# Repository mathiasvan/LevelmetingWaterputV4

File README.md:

# Levelmeting Waterput V4

## Description

This project is V4 in the levelmeting waterput project. It uses the [QDY30A level sensor with RS485 protocol](https://nl.aliexpress.com/item/1005004940352922.html?srcSns=sns_Copy&spreadType=socialShare&bizType=ProductDetail&social_params=60985872337&aff_fcid=d36cea4a44db45c6bede2523cc9afb1e-1753980282806-07628-_EjQJvbW&tt=MG&aff_fsk=_EjQJvbW&aff_platform=default&sk=_EjQJvbW&aff_trace_key=d36cea4a44db45c6bede2523cc9afb1e-1753980282806-07628-_EjQJvbW&shareId=60985872337&businessType=ProductDetail&platform=AE&terminal_id=5ec7fe4f4f894db8bbb9257240edc8ba&afSmartRedirect=y) because all the previous sensors broke.

This project uses the [ModbusMaster library](https://github.com/4-20ma/ModbusMaster/tree/master) which can be installed from the Library Manager in the Arduino IDE.

## Components

- Sensor is the [QDY30A level sensor with RS485 protocol](https://nl.aliexpress.com/item/1005004940352922.html?srcSns=sns_Copy&spreadType=socialShare&bizType=ProductDetail&social_params=60985872337&aff_fcid=d36cea4a44db45c6bede2523cc9afb1e-1753980282806-07628-_EjQJvbW&tt=MG&aff_fsk=_EjQJvbW&aff_platform=default&sk=_EjQJvbW&aff_trace_key=d36cea4a44db45c6bede2523cc9afb1e-1753980282806-07628-_EjQJvbW&shareId=60985872337&businessType=ProductDetail&platform=AE&terminal_id=5ec7fe4f4f894db8bbb9257240edc8ba&afSmartRedirect=y).
- [MAX485 module](https://nl.aliexpress.com/item/1005009235324836.html?spm=a2g0o.productlist.main.18.6f7028e663hk5b&algo_pvid=be4b66e5-2800-47ac-b6a6-58f13e3ffc2b&algo_exp_id=be4b66e5-2800-47ac-b6a6-58f13e3ffc2b-17&pdp_ext_f=%7B%22order%22%3A%22-1%22%2C%22eval%22%3A%221%22%7D&pdp_npi=4%40dis%21EUR%2117.32%215.53%21%21%21139.11%2144.42%21%40211b430817539750750754094efdc0%2112000048420270373%21sea%21BE%210%21ABX&curPageLogUid=VVom2pkc4jR8&utparam-url=scene%3Asearch%7Cquery_from%3A) so that the Arduino/ESP32 can communicate with the modbus protocol by using the RX and TX pins.
- AZDelivery ESP32 Dev Kit C V4 for wireless data transmission which I had lying around.
- [220-240V to 24V power adapter](https://www.amazon.com.be/-/en/Universal-Adapter-220-240V-Inverter-Converter/dp/B0DRP7CS6Y/ref=sr_1_6?crid=1ACSXPUVS5M3O&dib=eyJ2IjoiMSJ9.FTbxj5E1wm82PugM4UbSTGT1U-mJWSjutiHkte5HbkOeKfQrB-BOpuIBgImuRtzR-Oxsbv6aAav57drT663OdneUMQ0v3lXwz_fyhLJ6fqaBDiDpmi3t64ZKGnJhwVYG2fniTcgwXYQBbRFDHbBWO10F0hNb3RetDSqDfkFQakxUy2J-pAYLw4MWh0_5NM9YgepXiq3lA2xNkwteyM8PkXWb3mjuG0ey11ltC3uAtEaBidy8vM2pcyvCirzr-JK_tczkhxNdXqsYSO3U6uUHg2HoZKGJPsb2ADYXPQJMeao.7CeGK0aJhAgOUL4NGwdO5NkmGQ1lxo9eezmmLnGFa6c&dib_tag=se&keywords=240v%2BAC%2Bto%2B24v%2Bdc%2Badapter&qid=1756312614&sprefix=240v%2Bac%2Bto%2B24v%2Bdc%2Badapter%2Caps%2C95&sr=8-6&th=1) as the sensor works on 24V.
- [24V to 5V step-down converter](https://www.amazon.com.be/-/en/Heemol-Converter-Module-DC-DC-Power/dp/B0BCV6GRH5/ref=sr_1_3?crid=1N3TF49LMAD7M&dib=eyJ2IjoiMSJ9.q-0kuL72pe2IKbCABHzv8yXOsoQ4-v-Wq0jyu740BLkh13zqbLLy1FTG98uMWzEd8oz7OTgdK4OSP_4BK1gTu9wjp9CoapG2o3FZpXtIWlHqLC9P6f17gwq7Obhck1AqX469Dt1Ga9VJU1P0AJyKzVB0Ln-N5Ue2JrF5tVuZJ5tERdzsEsNTRxSBOX8tx5-2qo5J622tHXK5aL6bRXPW_Zn6CSXFCy_SFn3BGmzdMCV8JSYf2uHlnAjMfwTZvKOJRcqpMr4RmKVLJPQKJ-YGLqcOWeauEC0VQ_aWCukiv7Q.-T0r3asJ5W8xXmG-Gu4cFkVHnN3vhC2m68qT4c__YZo&dib_tag=se&keywords=dc+dc+24+to+5v+converter&qid=1756310998&sprefix=dc+dc+24+to+5v+converter%2Caps%2C92&sr=8-3) to power the ESP32. The MAX485 module is powered by the 5V pin of the ESP32.

## Diagram

Thanks lejmr for this diagram. I used it to test my sensor. It is wrong for the TX and RX pins, they should be swapped. (See below for more.) The rest is the same as in this diagram.

My adaptation:
I used pin 2 on the ESP32 to connect the DE and RE pins from the MAX485 module.

See the final KiCad diagram under the `waterputv4Schematics` folder. Here is a screenshot in case you don't have KiCad.

## Testing the sensor

This took a lot of trial and error but I got it working in the end. Some important remarks:

1. R0 from the MAX485 module should be connected to RX on the ESP32 and DI to TX. This is wrong in the original diagram I used.
2. The provided screw terminals on the MAX485 module are useful to connect the sensor to.
3. You cannot use the Serial port for debugging as you need the TX and RX pins to communicate with the sensor. I used the Bluetooth Serial library instead. You need to download the Bluetooth Serial app on your phone to connect to the wireless Serial.
4. When uploading the code, disconnect TX, RX, 5V and GND from the MAX485 and ESP32.
5. The test code is in the folder `testcode`.

## Final integration

- I have been using ThingSpeak for all the previous versions and it works quite well to store the data.
- The Bluetooth Serial library took too much space, so I have switched to the TelnetStream library. You need to install PuTTY and enter the IP adress which can be obtained from the Serial monitor. After this, it connects to the modbus sensor and from that moment on, all logging will happen with the telnet stream on PuTTY.
- You need to add a `credentials.h` file in the same folder as the final code. You need to fill this template with your own credentials.

```c++
#define mySSID "xxxxx"
#define myPASSWORD "xxxxx"
#define myChannelNumber 111111
#define myWriteAPIKey "xxxxxx"
```

## Telnet Commands

After connecting to your ESP32 using PuTTY (see IP address in Serial Monitor), you can use the following commands in the telnet console:

- **ping**  
  The ESP32 will respond with `pong`, show the current sensor height, and display the time remaining until the next automatic data upload to ThingSpeak.

- **send data**  
  Immediately triggers a sensor reading and uploads the value to ThingSpeak, regardless of the regular upload interval.

**Example session:**

```
> ping
pong
Doing a height reading...
Data at adress 4: 158
Converted height: 15.8cm
15.80
Time to next data send: 122 seconds

> send data
Sending data now...
Data at adress 4: 158
Converted height: 15.8cm
Height: 15.8cm
Uploading data to ThingSpeak...
Successful upload to ThingSpeak.
Height: 15.80 uploaded to ThingSpeak server.

```

If you enter an unknown command, nothing will happen. Commands are case-sensitive.

**Tip:**  
Make sure you have connected to the correct IP address and that your ESP32 is powered and connected to WiFi.

## Wishlist

- [ ] Add `reconnect wifi` command.
- [ ] OTA updates

## Resources

- [Datasheets that came in the box](https://h5.hlcode.com.cn/?id=NK1LFtJ&f=wx)
- [Thanks a lot to lejmr for this project!](https://github.com/lejmr/dyi-ha-water-management)
- [This tutorial has helped me a lot](https://how2electronics.com/how-to-use-modbus-rtu-with-esp32-to-read-sensor-data/)

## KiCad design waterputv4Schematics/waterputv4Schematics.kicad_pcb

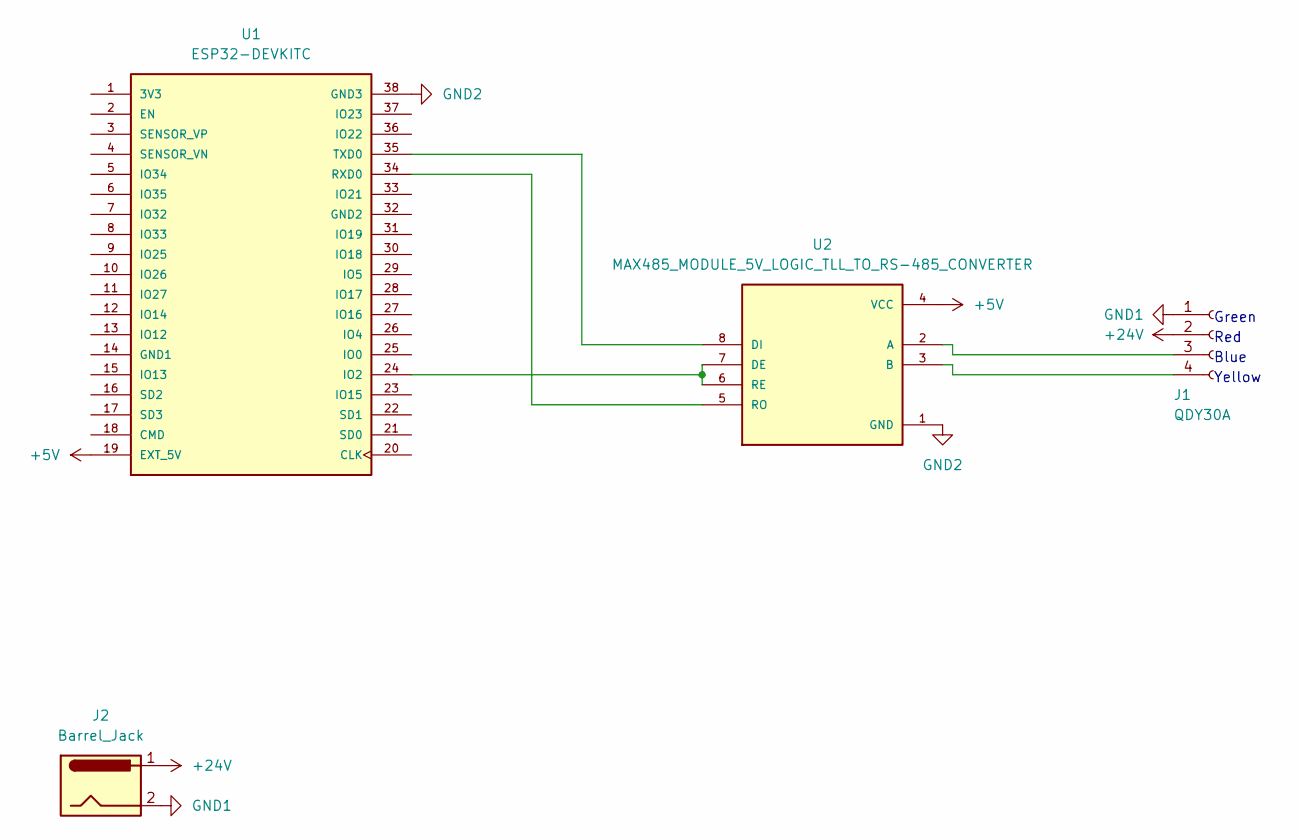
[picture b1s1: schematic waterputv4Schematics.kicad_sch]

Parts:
J1: QDY30A
J2: Barrel_Jack; BarrelJack_Horizontal
U1: ESP32-DEVKITC; MODULE_ESP32-DEVKITC; PARTREV N/A
U2: MAX485_MODULE_5V_LOGIC_TLL_TO_RS-485_CONVERTER; MODULE_MAX485_MODULE_5V_LOGIC_TLL_TO_RS-485_CONVERTER; PARTREV 1r0

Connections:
+5V: U1.19 (EXT_5V), U2.4 (VCC)
+24V: J1.2, J2.1
GND1: J1.1, J2.2
GND2: U1.38 (GND3), U2.1 (GND)
unnamed: U1.24 (IO2), U2.6 (RE), U2.7 (DE)
unnamed: U1.34 (RXD0), U2.5 (RO)
unnamed: U1.35 (TXD0), U2.8 (DI)
unnamed: J1.3, U2.2 (A)
unnamed: J1.4, U2.3 (B)

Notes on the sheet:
Red
Blue
Yellow
Green

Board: 2 copper layers, 4 parts (0 on the bottom side), 9 nets, no tracks yet.

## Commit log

2025-09-04 Testcode and first diagram complete
2025-09-15 Final code
2025-09-15 Fix for screenshot of schematic image readme
2025-09-15 Actual fix of screenshot of schematic readme
2025-09-16 Added ping so that you can troubleshoot within data uploads
2025-09-16 Added send data command
2025-09-16 Fix for unkown command bug
2025-09-16 Improved documentation and small fixes
2025-09-21 added wishlist
2025-09-21 updated wishlist
2026-04-18 fix for wrong link
